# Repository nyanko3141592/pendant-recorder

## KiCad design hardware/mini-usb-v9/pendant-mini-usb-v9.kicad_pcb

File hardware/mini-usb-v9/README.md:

# Mini USB v9 — 回路・丸形収納の比較試作

2026-10-25。USB-Cデータ書き出し＋充電、連続16時間、専用台なし、無線なしを維持する設計案。**発注不可。** 回路図と実フットプリント配置は更新したが、配線完成版ではない。

## 今回の変更

- 実装80点→68点（パッド等を含め74フットプリント）。STM32U535CEU6のQFN48は維持。高価なWLCSP/HDIへの変更を避け、4層の配線成立性を試験中。4層化は未資格化。
- T5838＋TXS0104E＋1.8V LDOを、3.3V直結PDMのIM69D130に変更。AAD/WAKE/THSELを削除。0.768MHz・16kHz/48倍デシメーションを評価候補とする。低電力モードはSNR64dBで、静かな声の音質と電力を実機比較する。データシートの0.3mAは1.8V条件であり、3.3Vでの実測値ではない。
- BQ25185で充電と電源切替を統合。24kΩで4.2V/入力100mA、15kΩで充電20mA候補。SYS10µFの実効容量、ISET10nF、低電圧・ピーク負荷は要検証。
- 温度保護は削除しない。TLV7042の2つのオープンドレイン出力でQ4ゲートをクランプ。MCU許可信号→10kΩ→ゲート、ゲート100kΩプルダウン。冷・熱のどちらか異常ならゲートLow、Q4 OFF、CEのVBUS100kΩプルアップで充電停止。MCUリセット時も許可なし。理想論理のみ確認、POR/瞬断/短絡/公差は未資格化。
- 電池NTCは外部窓比較器で監視。BQ25185内蔵TSの固定10kΩを温度センサー扱いしない。既存10k/B3370仮定の狭い充電窓（公称約20–30℃）を保持。実際のパック仕様が未確定なので設定値も最終値ではない。
- LEDを1個に集約。表示要求時の点滅で残量表示、常時点灯を避ける。
- 記憶容量を4GB→512MiBのCSNP4GCR01-DPWに変更した価格削減候補。LCSC公開表示は欠品。データシートのピン配置は確認済みだがフットプリント製造受理は未確認。4GB版への復帰は同じ収納包絡内で可能性があるものの、ランド再照合が必要。

## 収納

新案26×28×14mm、平面R12.9、縁R2。旧印刷基準26×31×14mm・R5を上書きしていない。正面面積は約25.4%減。OmiのD25.5×15mm寸法包絡比では正面面積約14.6%増。Omi模型は円筒の寸法ゲージで、実製品CADではない。

基板は24×26mmカプセルをUSB側y=24.5mmで切った形。0.8mm厚、下面z=8.5mm。電池15×17×6mm、100mAh候補包絡は維持。低い部品を基板裏に回し、電池上端との公称隙間を確保。電池の保護基板・完成リード・コネクタ配線・膨張公差は未資格化。ケースはテープ仮止め、2点仮支持で、量産用の爪・紐穴・防水・音道シールではない。

## 検査結果

- `erc.json`: ERC 0。
- `drc.json`: 未配線配置原本の幾何DRC 0、回路図等価性0、未配線175件。これを配線済みと扱わない。
- `route-trial.kicad_pcb`: 4層の試験配線。`route-trial-drc.json`に15違反、5未接続。GND面・USB差動/リターンパス・デカップリング配線の再設計が必要。製造用Gerberは出していない。
- 実部品の寸法ではなく、フットプリント外接矩形＋仮高さの保守的な立体包絡。ケース/蓋と部品/電池に重なりなし。部品と電池も重なりなし。支持面の接触あり。
- 5組のSTL/3MFで閉メッシュ、法線整合、単一接続体、正体積、Z=0、mm単位を確認。全三角形間の自己交差を網羅検査したものではない。
- Bambu A1 mini 0.4/PLA/0.2mm/3壁/15%/サポートありで4部品スライス完了。推定23分1秒・5.04g。プリンタ送信/物理印刷は未実施。

## 16時間の条件とトレードオフ

100mAhの70%を使えると仮定すると、平均消費電流は4.375mA以下が必要。達成は未実測。電池の容量を先に減らしていない。

512MiBでは16kHzモノラルIMA-ADPCM、10秒ごとのWAVをage v1暗号化、4KiBクラスタ・暗号化余裕1KiB/区間と仮定し16時間で495,452,160byte。FS予備16MiBを引いた残りは24,641,536byte。実CSD容量/実ファイルサイズ/空き容量検査が必要で、複数日録音や16時間PCM16には使えない。自動削除・上書きはしない。

## 資料

- `pendant-mini-usb-v9.kicad_sch` / `schematic.pdf` / `design.json`: ピン単位回路原本。
- `pendant-mini-usb-v9.kicad_pcb`: 未配線配置原本。`route-trial.*`は別の試験。
- `connections.csv` / `bom.csv`: 設計確認用。JLC発注承認済みBOMではない。
- `review.json`: 電力・容量の算術、理想論理表、発注前と実機の残件。
- モデル: `/Users/takahashinaoki/Downloads/Pendant-mini-usb-v9/`
- 比較原本: `/Users/takahashinaoki/Downloads/Pendant-rounded-fit-v7/`
- 再生成スクリプトは配置/回路を上書きする。手修正後には無条件で再実行しない。

## 出典・調達の状態

2026-10-25閲覧。カタログ掲載は在庫確保・見積り画面の照合完了を意味しない。

- [Infineon IM69D130 datasheet](https://www.infineon.com/dgdl/Infineon-IM69D130-DS-v01_00-EN.pdf): 3.3V直結、PDM、端子、低電力モードの根拠。JLC候補[C536262](https://jlcpcb.com/partdetail/InfineonTechnologies-IM69D130V01/C536262)。末尾発注品番との同一性を要確認。
- [TI BQ25185 datasheet](https://www.ti.com/lit/ds/symlink/bq25185.pdf): 端子・設定・電源経路。JLC候補[C19725033](https://jlcpcb.com/partdetail/TexasInstruments-BQ25185DLHR/C19725033)。[LCSC参考](https://www.lcsc.com/product-detail/C19725033.html?s_z=n_MS2548)は1個$1.7472の表示、PCBA価格ではない。
- [TI TLV7042](https://www.ti.com/product/TLV7042/part-details/TLV7042DDFR): オープンドレイン出力。[LCSC C2867856](https://www.lcsc.com/de/product-detail/C2867856.html)。在庫表示がページ間で相違し未確定。
- [CSNP4GCR01-DPW](https://www.lcsc.com/product-detail/C50396672.html): 512MiB、公開表示欠品・1個参考$12.4734。旧4GBの途中JLC見積り約$40.16/個より低い参考値だが、今回の購入可能価格ではない。総額が安くなることは未確認。
- [Omi consumer hardware](https://docs.omi.me/doc/hardware/consumer): 小型基板、SD NAND、電池と基板の重ね方を参照。専用充電台/無線/HDI加工をそのまま採用していない。

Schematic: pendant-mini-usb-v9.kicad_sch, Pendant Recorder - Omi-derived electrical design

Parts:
C1, C2, C3, C6, C9, C22, C26: 100n; C_0402_1005Metric
C4: 10u; C_0603_1608Metric
C5: 4.7u; C_0603_1608Metric
C7, C16, C25: 1u; C_0402_1005Metric
C11, C12: 10p tentative; C_0402_1005Metric
C13: 2.2u 10V; C_0402_1005Metric
C14: 2.2u; C_0402_1005Metric
C15: 10u 10V effective >=1u; C_0603_1608Metric
C27: 22u effective TBD; C_0603_1608Metric
C28: 10n; C_0402_1005Metric
C29: 100n 10V; C_0402_1005Metric
C30: 10n tentative; C_0402_1005Metric
D6: amber LED 0402 TBD; LED_0402_1005Metric
J1: USB4105-GF-A (candidate); USB_C_GCT_USB4105_GroundLand112
J2: 0781710003 / 100mAh protected NTC pack TBD; Molex_Pico-EZmate_78171-0003_1x03-1MP_P1.20mm_Vertical
J3: TC2030 SWD target pads; Tag-Connect_TC2030-IDC-NL_2x03_P1.27mm_Vertical
Q3: 2N7002 (VBUS detect); SOT-23
Q4: 2N7002; SOT-23
R1: 0R; R_0402_1005Metric
R2: 10k; R_0402_1005Metric
R3, R4, R12, R13, R15, R22, R36: 100k; R_0402_1005Metric
R6, R7: 5.1k 1%; R_0402_1005Metric
R8, R9: 0R tuning; R_0402_1005Metric
R10: 15k 1%; R_0402_1005Metric
R11: 20k 1%; R_0402_1005Metric
R14: 1M; R_0402_1005Metric
R21, R23: 22R tentative; R_0402_1005Metric
R24, R25, R28: 47k; R_0402_1005Metric
R32: 6.8k tentative; R_0402_1005Metric
R33, R34: 1M 1%; R_0402_1005Metric
R35, R37, R38, R40, R43: 10k 1%; R_0402_1005Metric
R39: 12.1k 1%; R_0402_1005Metric
R41: 8.25k 1%; R_0402_1005Metric
R42: 24k 1%; R_0402_1005Metric
SW1: B3U-1000P (candidate); SW_SPST_B3U-1000P
TP1, TP2, TP3, TP5, TP6: TestPoint; TestPoint_Pad_D1.0mm
U1: STM32U535CEU6; QFN-48-1EP_7x7mm_P0.5mm_EP5.6x5.6mm
U2: USBLC6-2P6; SOT-666
U3: BQ25185DLHR; Texas_DLH0010A_WSON-10-1EP_2.2x2mm_P0.4mm_EP0.9x1.5mm
U4: TPS7A0233PDBVR; SOT-23-5
U8: IM69D130V01XTSA1; Infineon_PG-LLGA-5-1
U10: TPS22916CYFPR; TPS22916_YFP4
U11: CSNP4GCR01-DPW; CSNP4GCR01_DPW_LGA8
U12: TLV7042DDFR; SOT-23-8
Y1: 32.768kHz CL=7pF TBD; Crystal_SMD_2012-2Pin_2.0x1.2mm

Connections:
/BAT: C14.1, J2.1 (PACK+), R33.1, TP1.1, U3.2 (BAT)
/BAT_ADC: C28.1, R33.2, R34.1, U1.11 (PA1)
/BAT_TS: J2.2 (PACK_NTC), R37.2, U12.2 (INA-), U12.5 (INB+)
/BOOT0: R3.1, U1.44 (PH3)
/BUTTON_N: R4.2, SW1.1, U1.26 (PB13)
/CC1: J1.A5 (CC1), R6.1
/CC2: J1.B5 (CC2), R7.1
/CHARGER_TS: R35.1, U3.6 (TS_MR)
/CHG_ALLOW: R43.1, U1.20 (PB2)
/CHG_GUARD_GATE: Q4.1 (G), R36.1, R43.2, U12.1 (OUTA), U12.7 (OUTB)
/CHG_INHIBIT_GATE: Q4.3 (D), R12.2, U3.4 (CE_N)
/CHG_N: R11.2, U1.27 (PB14), U3.9 (STAT1)
/GND: C1.2, C2.2, C3.2, C4.2, C5.2, C6.2, C7.2, C9.2, C11.2, C12.2, C13.2, C14.2, C15.2, C16.2, C22.2, C25.2, C26.2, C27.2, C28.2, C29.2, C30.2, D6.1 (K), J1.A1 (GND), J1.A12 (GND), J1.B1 (GND), J1.B12 (GND), J1.SH (SHIELD), J2.3 (PACK-), J3.5 (GND), Q3.2 (S), Q4.2 (S), R3.2, R6.2, R7.2, R10.2, R14.2, R22.2, R34.2, R35.2, R36.2, R39.2, R41.2, R42.2, SW1.2, TP6.1, U1.8 (VSSA), U1.23 (VSS), U1.35 (VSS), U1.47 (VSS), U1.49 (VSS), U2.2 (GND), U3.5 (GND), U3.11 (EP), U4.2 (GND), U8.4 (SELECT), U8.5 (GND), U10.B1 (GND), U11.4 (VSS), U12.4 (VEE)
/ILIM_VSET: R42.1, U3.7 (ILIM_VSET)
/ISET: C30.1, R10.1, U3.8 (ISET)
/LSE_IN: C11.1, U1.3 (PC14), Y1.1
/LSE_OUT: C12.1, U1.4 (PC15), Y1.2
/NRST: C9.1, J3.3 (nRESET), R2.2, U1.7 (NRST)
/PDM_CLK: R21.2, U8.3 (CLOCK)
/PDM_CLK_MCU: R21.1, U1.39 (PB3)
/PDM_DATA: U1.40 (PB4), U8.1 (DATA)
/SD_CLK: R23.2, U11.3 (CLK)
/SD_CLK_MCU: R23.1, U1.15 (PA5)
/SD_CS_N: R28.2, U1.14 (PA4), U11.2 (CS_N)
/SD_EN: R22.1, U1.18 (PB0), U10.B2 (ON)
/SD_MISO: R25.2, U1.16 (PA6), U11.6 (DO)
/SD_MOSI: R24.2, U1.17 (PA7), U11.5 (DI)
/SD_V3: C26.1, C27.1, R24.1, R25.1, R28.1, TP5.1, U10.A1 (VOUT), U11.8 (VCC)
/STATUS_LED: R32.1, U1.29 (PA8)
/STATUS_LED_A: D6.2 (A), R32.2
/SWCLK: J3.4 (SWCLK), U1.37 (PA14)
/SWDIO: J3.2 (SWDIO), U1.34 (PA13)
/SYS: C15.1, TP2.1, U3.1 (SYS), U4.1 (IN), U4.3 (EN)
/TS_COLD_REF: R38.2, R39.1, U12.3 (INA+)
/TS_HOT_REF: R40.2, R41.1, U12.6 (INB-)
/USB_DM: J1.A7 (D-), J1.B7 (D-), R9.1, U2.3 (IO2), U2.4 (IO2)
/USB_DM_MCU: R9.2, U1.32 (PA11)
/USB_DP: J1.A6 (D+), J1.B6 (D+), R8.1, U2.1 (IO1), U2.6 (IO1)
/USB_DP_MCU: R8.2, U1.33 (PA12)
/V3V3: C1.1, C2.1, C3.1, C4.1, C16.1, C22.1, C25.1, J3.1 (VTref), R1.1, R2.1, R4.1, R11.1, R15.1, TP3.1, U1.1 (VBAT), U1.24 (VDD), U1.36 (VDD), U1.48 (VDD), U4.5 (OUT), U8.2 (VDD), U10.A2 (VIN)
/VBUS: C13.1, C29.1, J1.A4 (VBUS), J1.A9 (VBUS), J1.B4 (VBUS), J1.B9 (VBUS), R12.1, R13.1, R37.1, R38.1, R40.1, U2.5 (VBUS), U3.10 (IN), U12.8 (VCC)
/VBUS_GATE: Q3.1 (G), R13.2, R14.1
/VBUS_N: Q3.3 (D), R15.2, U1.10 (PA0)
/VCAP: C5.1, U1.22 (VCAP)
/VDDA: C6.1, C7.1, R1.2, U1.9 (VDDA)

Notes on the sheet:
01 MCU / RTC / UI
02 USB-C / CHARGER
03 POWER / FUEL GAUGE
04 AUDIO / SD / INDICATORS
ENGINEERING DRAFT - NOT FOR FABRICATION - See hardware/mini-usb-v9/README.md

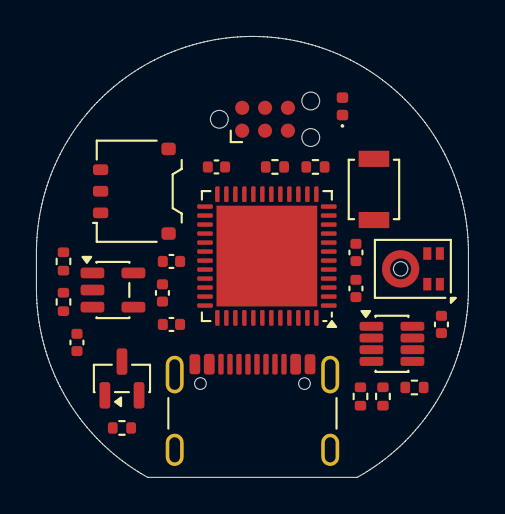
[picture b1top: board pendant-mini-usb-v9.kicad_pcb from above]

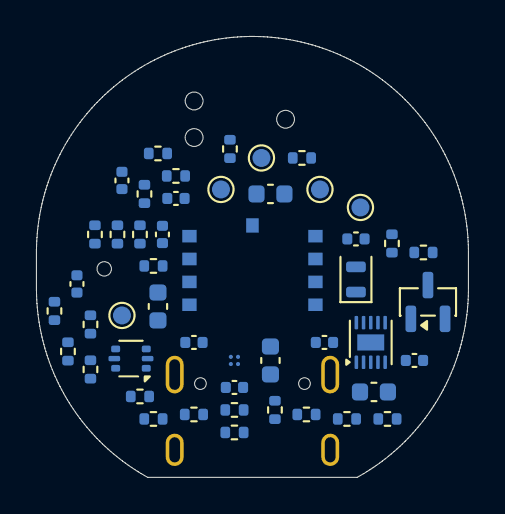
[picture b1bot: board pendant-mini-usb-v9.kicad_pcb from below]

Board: 4 copper layers, 24.0 x 24.5 mm, 74 parts (48 on the bottom side), 45 nets, no tracks yet.

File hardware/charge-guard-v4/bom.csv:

Reference,Part/value,Footprint,Design note
U1,STM32U535CEU6,Package_DFN_QFN:QFN-48-1EP_7x7mm_P0.5mm_EP5.6x5.6mm,512KB Flash/274KB RAM; non-SMPS UFQFPN48. PB3/PB4 ADF AF3; PA5/6/7 SPI1 AF5. VDD USB shared 3.3V. JLC acceptance and pin review pending.
C1,100n,Capacitor_SMD:C_0402_1005Metric,
C4,10u,Capacitor_SMD:C_0603_1608Metric,Main bulk capacitor; check startup and effective capacitance.
C9,100n,Capacitor_SMD:C_0402_1005Metric,
R2,10k,Resistor_SMD:R_0402_1005Metric,
Y1,32.768kHz CL=7pF TBD,Crystal:Crystal_SMD_2012-2Pin_2.0x1.2mm,
C11,10p tentative,Capacitor_SMD:C_0402_1005Metric,
C12,10p tentative,Capacitor_SMD:C_0402_1005Metric,
J3,TC2030 SWD target pads,Connector:Tag-Connect_TC2030-IDC-NL_2x03_P1.27mm_Vertical,TC2030-NL/CTX standard; completed STM32-compatible probe/cable; access with battery disconnected.
SW1,B3U-1000P (candidate),Button_Switch_SMD:SW_SPST_B3U-1000P,
R4,100k,Resistor_SMD:R_0402_1005Metric,
R5,3.3k,Resistor_SMD:R_0402_1005Metric,
D1,red LED,LED_SMD:LED_0402_1005Metric,
J1,USB4105-GF-A (candidate),PendantD1:USB_C_GCT_USB4105_GroundLand112,Exact footprint and shield pad numbering pending connector selection
R6,5.1k 1%,Resistor_SMD:R_0402_1005Metric,
R7,5.1k 1%,Resistor_SMD:R_0402_1005Metric,
R8,0R tuning,Resistor_SMD:R_0402_1005Metric,STM32 integrated USB termination; external series value validate against ST USB layout guidance.
R9,0R tuning,Resistor_SMD:R_0402_1005Metric,STM32 integrated USB termination; external series value validate against ST USB layout guidance.
U2,USBLC6-2P6,Package_TO_SOT_SMD:SOT-666,"ST DS4260 same 6-pin function diagram; smaller package, LCSC C15999 catalog; orientation/land pattern final audit pending."
C13,2.2u 10V,Capacitor_SMD:C_0402_1005Metric,
U3,BQ25101YFPR,Pendant:BQ25101_YFP6,BQ25101 charge regulation retained; TS driven by independent hardware window guard and fixed10k. Not directly connected to pack NTC.
R10,6.19k 1%,Resistor_SMD:R_0402_1005Metric,"Nominal21.81mA, upper estimate23.66mA. XE charge current/termination/voltage acceptance not finalized."
R11,100k,Resistor_SMD:R_0402_1005Metric,
C14,2.2u,Capacitor_SMD:C_0402_1005Metric,
J2,0781710003 / DTP401525-XE,Connector_Molex:Molex_Pico-EZmate_78171-0003_1x03-1MP_P1.20mm_Vertical,"Pack NTC goes to separate window comparator, not charger TS. Beta/tolerances need supplier confirmation."
Q2,2N7002 (charge inhibit),Package_TO_SOT_SMD:SOT-23,Default-on TS clamp. Only MCU permission AND both hardware temperature permissions release it. Validate start-up transients.
R12,100k,Resistor_SMD:R_0402_1005Metric,100k VBUS pull-up defaults Q2 to charge inhibited; no MCU GPIO connection to5V.
D2,BAT54WS (candidate; leakage/forward drop review pending),Diode_SMD:D_SOD-323,USB path; characterize leakage and input inrush
Q1,DMP2035U (candidate; power path review pending),Package_TO_SOT_SMD:SOT-23,"S=SYS, D=BAT intentionally; body diode BAT -> SYS; exact MPN/pinout pending"
R16,100k,Resistor_SMD:R_0402_1005Metric,
C15,4.7u,Capacitor_SMD:C_0603_1608Metric,
U4,TPS7A0233PDBVR,Package_TO_SOT_SMD:SOT-23-5,3.3V main rail: 48-pin MCU has no separate USB supply; dropout/capacity measurement required.
U6,TPS7A0218PDBVR,Package_TO_SOT_SMD:SOT-23-5,DBV / SOT23-5 prototype; miniaturization later
C16,1u,Capacitor_SMD:C_0402_1005Metric,
C18,1u,Capacitor_SMD:C_0402_1005Metric,
C19,1u,Capacitor_SMD:C_0402_1005Metric,
R17,100k,Resistor_SMD:R_0402_1005Metric,
U8,T5838,Pendant:T5838_LGA7_BottomPort,BOTTOM port; 1.62..1.98V only; SELECT low = right channel
U9,TXS0104ERUTR,Package_DFN_QFN:Texas_R-PUQFN-N12,TI SCES651K Table 5-4 RUT pinout. UQFN procurement and PCBA acceptance pending.
R21,22R tentative,Resistor_SMD:R_0402_1005Metric,
C22,100n,Capacitor_SMD:C_0402_1005Metric,
C23,100n,Capacitor_SMD:C_0402_1005Metric,
C24,100n,Capacitor_SMD:C_0402_1005Metric,
U10,TPS22916CYFPR,Pendant:TPS22916_YFP4,Omi SD switch; power-off sequence must tristate ALL SD signals
R22,100k,Resistor_SMD:R_0402_1005Metric,
C25,1u,Capacitor_SMD:C_0402_1005Metric,
U11,CSNP32GCR01-BOW,Pendant:CSNP32GCR01_LGA8,SPI mode per manufacturer p2; unused DAT1/DAT2 reserved; verify power-up and interrupted-write behavior.
R23,22R tentative,Resistor_SMD:R_0402_1005Metric,
R24,47k,Resistor_SMD:R_0402_1005Metric,
R25,47k,Resistor_SMD:R_0402_1005Metric,
R28,47k,Resistor_SMD:R_0402_1005Metric,
C26,100n,Capacitor_SMD:C_0402_1005Metric,
C27,22u effective TBD,Capacitor_SMD:C_0603_1608Metric,
TP1,TestPoint,TestPoint:TestPoint_Pad_D1.0mm,
TP2,TestPoint,TestPoint:TestPoint_Pad_D1.0mm,
TP3,TestPoint,TestPoint:TestPoint_Pad_D1.0mm,
TP4,TestPoint,TestPoint:TestPoint_Pad_D1.0mm,
TP5,TestPoint,TestPoint:TestPoint_Pad_D1.0mm,
TP6,TestPoint,TestPoint:TestPoint_Pad_D1.0mm,
R32,6.8k tentative,Resistor_SMD:R_0402_1005Metric,"LED current target 0.1-0.2mA; verify LED Vf, daylight readability and GPIO limits"
D6,amber LED 0402 TBD,LED_SMD:LED_0402_1005Metric,Battery level by blink count; shared charging/error indication; exact LED MPN pending.
C2,100n,Capacitor_SMD:C_0402_1005Metric,
C3,100n,Capacitor_SMD:C_0402_1005Metric,
C5,4.7u,Capacitor_SMD:C_0603_1608Metric,
C6,100n,Capacitor_SMD:C_0402_1005Metric,
C7,1u,Capacitor_SMD:C_0402_1005Metric,
R1,0R,Resistor_SMD:R_0402_1005Metric,
R3,100k,Resistor_SMD:R_0402_1005Metric,
Q3,2N7002 (VBUS detect),Package_TO_SOT_SMD:SOT-23,
R13,100k,Resistor_SMD:R_0402_1005Metric,
R14,1M,Resistor_SMD:R_0402_1005Metric,
R15,100k,Resistor_SMD:R_0402_1005Metric,
R33,1M 1%,Resistor_SMD:R_0402_1005Metric,"Battery divider 1:2; sample after settling, calibrate with VREFINT; not coulomb counting."
R34,1M 1%,Resistor_SMD:R_0402_1005Metric,"Battery divider 1:2; sample after settling, calibrate with VREFINT; not coulomb counting."
C28,10n,Capacitor_SMD:C_0402_1005Metric,"Battery divider 1:2; sample after settling, calibrate with VREFINT; not coulomb counting."
R35,10k 1%,Resistor_SMD:R_0402_1005Metric,Holds normal TS level when released; no floating TS/TTDM in intended circuit.
R36,100k,Resistor_SMD:R_0402_1005Metric,MCU reset/high-Z defaults to no charging permission.
R37,10k 1%,Resistor_SMD:R_0402_1005Metric,Ratiometric NTC excitation only while USB present; self-heating must be verified.
R38,10k 1%,Resistor_SMD:R_0402_1005Metric,
R39,12.1k 1%,Resistor_SMD:R_0402_1005Metric,Provisional narrow window. Final values require actual pack R-T curve.
R40,10k 1%,Resistor_SMD:R_0402_1005Metric,
R41,8.25k 1%,Resistor_SMD:R_0402_1005Metric,Provisional narrow window. Final values require actual pack R-T curve.
U12,TLV7032DDFR,Package_TO_SOT_SMD:SOT-23-8,Push-pull variant intentionally selected: POR outputs low. Do not substitute TLV7042 open-drain (POR high-Z). TI SLVSE13J pinout table4-2.
Q4,2N7002,Package_TO_SOT_SMD:SOT-23,Series pull-down permission chain. All three must conduct to release Q2. Body diodes oppose pull-down when off. Verify stack/leakage/transients.
Q5,2N7002,Package_TO_SOT_SMD:SOT-23,Series pull-down permission chain. All three must conduct to release Q2. Body diodes oppose pull-down when off. Verify stack/leakage/transients.
Q6,2N7002,Package_TO_SOT_SMD:SOT-23,Series pull-down permission chain. All three must conduct to release Q2. Body diodes oppose pull-down when off. Verify stack/leakage/transients.
C29,100n 10V,Capacitor_SMD:C_0402_1005Metric,Place adjacent to U12 supply pins.

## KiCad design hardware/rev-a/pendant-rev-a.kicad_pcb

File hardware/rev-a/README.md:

# Pendant Recorder Rev A1 — 回路・配置レビュー用

> 製造方針: [JLCPCBで部品実装まで依頼](../../docs/jlcpcb-assembly.md)。両面Standard PCBAを第一候補とし、実装用在庫・全フットプリント・製造レビューを確認して採用する。現回路の全品番受理は未確認。

2026-10-24。**未配線の配置検討版。発注不可。** 回路図から92部品を実寸フットプリントに割り当て、ネット接続付きの4層KiCad基板を作成した。20×34×0.8mmは現在の配置検討枠で、最小寸法や配線成立を示すものではない。

- [基板配置と製造上の課題](layout-review.md)
- [基板データ](pendant-rev-a.kicad_pcb)、[表面](placement-top.svg)、[裏面](placement-bottom.svg)
- [回路図プレビュー](pendant-rev-a.svg) / [検査記録](verification.md)
- `design.json`: 部品、端子、ネット、フットプリントの原本
- `Pendant.pretty/`: データシートから作成したフットプリント。製造監査は未完了
- `bom.csv` / `connections.csv`: 候補部品表と全端子接続表
- `placement-review.csv`: 配置確認用。JLC発注用CPLではない

既製DTP401525(PHR)110mAh（最大15.5×27×4.2mm、付属PHコネクタと配線は別枠）を第一候補とする。24時間録音・平均2mA以下は未実測の設計目標。旧円形26mmモデルや20×32×12mm案は、現配置が入ることを保証しない。

## 既存案からの必須修正

1. **STM32U535CBU6ではSDMMCを接続できない。** ST公式のUFQFPN48端子データにSDMMC信号がない。試作は **STM32U535RCT6 / LQFP64、内部LDO版**。PC8/9/10/11/12、PD2を使用する。22mm円形の量産候補はUFBGA64等を別途選定し、端子表と配置をやり直す。LQFP64案が22mmに収まるとは主張しない。
2. **T5838は1.8V専用、底面音孔。** 最新DS-000383 v1.2では1.62〜1.98V、絶対最大も1.98V。既存の3V直結案は不可。OmiのMIC1回路を参考に1.8V LDO＋TXS0104Eを入れた。基板の音孔とガスケットが必要。
3. USB PHYには **VBUSから専用3.3V LDO→VDDUSB**。録音用3.0Vとは分け、USBの電源条件を満たす設計とする。USB切断時のVDDUSB=0、電源監視・USB起動順序はST資料と実機で検証する。
4. BQ25101のBATにMSC負荷を直接ぶら下げない。USB中はD2からSYSへ給電し、Q1で電池からSYSへの経路を遮断する。これにより充電電流に同期中のシステム負荷が混ざるのを避ける。
5. 110mAh電池の充電設定は**約21.8mA**。RISET=6.19kΩ（1%）、135/6190=0.02181A。KISET最大145と抵抗公差から最大約23.66mA。パックの標準22mAに近づけ、最大55mAを下回る設定へ変更。充電時間はCC部分だけでも約5時間相当で、CVを含む時間は実測で確定する。

## Omiからの継承と差分

基準: `reference/omi/hardware-consumer/mainboard-schematic.pdf` の実際のタイトルは **OMI 2 v0.5、5ページ**。上流のフォルダ/READMEのv1.2表記と区別する。

| Omi回路 | 本設計 |
|---|---|
| Sheet 4 MIC1 T5838、1.8V、TXS0104E、100nF、SELECT=GND | 電圧と信号構成を継承。LDOを低Iq品へ変更。1マイクで開始 |
| Sheet 4 SD NAND + TPS22916、スイッチ後電源へのプルアップ | 継承。512MB→4GB、SPI→SDMMC 4bit。CMD/DAT0〜3の5本をプルアップ |
| Sheet 5 BQ25101、ISET、10k NTC、入出力2.2µF | 継承。約21.8mA設定、保護付きセル、外付け負荷分離、充電停止GPIO追加 |
| Sheet 2 SWD、32kHz水晶 | 構成を参考にし、STM32固有の端子とVCAPに変更 |
| 無線SoC、Wi-Fi、RF、IMU、振動モーター、磁気充電台 | 非搭載。USB-Cを本体へ直付け |
| 生セクタのリングバッファ | 不採用。FAT上の通常WAVファイル |

参照ファイルは改変せず、MITライセンスを保持している。

## 接続の要点

| 機能 | STM32ポート / LQFP64端子 | 接続 |
|---|---|---|
| SD DAT0/1/2/3 | PC8/9/10/11 = 39/40/51/52 | NAND 6/7/1/2 |
| SD CLK / CMD | PC12 / PD2 = 53/54 | 22Ω経由NAND 3 / NAND 5 |
| ADF CLK / DATA | PB3 / PB4 = 55/56 | TXS B4 / B3。PC10/11のADF機能はSDと競合するため使わない |
| MIC WAKE / THSEL | PA2 / PA3 = 16/17 | TXS B1 / B2 |
| USB D− / D+ | PA11 / PA12 = 44/45 | 22Ω仮値、ESD、USB-C両面端子 |
| I2C SCL / SDA | PB6 / PB7 = 58/59 | MAX17048、4.7kΩ→V3 |
| SWDIO / SWCLK | PA13 / PA14 = 46/49 | パッド。VTrefは電圧参照のみ |
| SD_EN / MIC_EN | PB0 / PB1 = 26/27 | 起動時プルダウンでOFF |
| USB検出 | PA0 = 14 | Q3経由、**VBUS_N=Lowで接続** |
| 電池割り込み / 充電状態 | PA1 / PB14 = 15/35 | Active low |
| 充電禁止 | PB2 = 28 | High→Q2→TSをGNDへ。通常はLow |
| 録音LED / ボタン | PB12 / PB13 = 33/34 | D1 High点灯、ボタンLow |
| 残量3点LED | PA4/5/6 = 20/21/22 | R29/30/31→D3/4/5、High点灯 |
| 状態LED | PA7 = 23 | R32→D6、High点灯。充電/同期/異常 |
| LSE | PC14/15 = 3/4 | 32.768kHz、容量は水晶確定後に計算 |

VDD 19/32/64はそれぞれ100nF、共通10µF。VCAP 30は4.7µFで他負荷禁止。VDDAは0Ω経由V3＋100nF/1µF。VBAT端子はV3で、電池直結ではない。保護遮断時はRTCを失う。

### 電源経路

- 持ち歩き: 保護済みBAT→Q1→SYS→3.0V LDO→MCU/SD。マイクのみ1.8V。
- USB接続: VBUS→D2→SYS。同時にVBUS→BQ25101→BAT、VBUS→3.3V LDO→VDDUSB。
- **Q1はsource=SYS、drain=BAT**。ボディダイオードをBAT→SYS向きにする。通常の高側スイッチと見た目が逆なのでフットプリント照合必須。gate=VBUS、100kΩでGNDへ。低VGSでのRDS(on)、逆漏れ、最大VGSを満たす型番は未選定。
- MAX17048は保護済みBATに接続。I2CプルアップはV3。保護セルが外れた際のI2C端子からの逆給電も確認対象。
- TSはセルに密着させた10k NTC。電池内蔵NTCとTH1を二重実装しない。NTCを省略したまま使用しない。
- セル保護は電池パックに要求する。BQ25101は過放電/短絡保護回路の代用にはならない。

### USBとSDの所有権

1. VBUS検出だけでは充電のみ。録音ON/OFFを維持し、SDはファームが所有する。同期要求（暫定: USB接続中にボタン2回押し）を受けて初めて録音DMA停止→WAVヘッダ確定→flush/sync→FAT unmount。
2. USB用電源を検証してPHY/MSC開始。MSC中はホストからのブロック要求だけがSDを使用し、ファームのファイル処理は動かさない。
3. USB切断後はMSC処理を停止してからFATをmount。`TIME.TXT`を検査してRTC設定、同期前の録音ON/OFFへ戻す。Macは安全な取り外しを行う。充電のみでの切断はSDを再mountしない。
   - データ接続のない充電器で同期操作をした場合、未接続タイムアウト後にMSCを停止し、ファームがSDを安全に再取得して元の録音状態へ戻す。
4. USB suspendでは充電禁止、SD停止、USB規定内への低消費電力化が必要。起動・未列挙時は総入力100mA以内を設計予算とし、50mA充電＋システムの最悪値を実測する。
5. SD電源OFFはsync/unmount後。CMD/DAT/CLKをHi-ZにしてプルアップはSD_V3のみ。再起動時は低速初期化とACMD6による4bit設定を行う。
6. 電圧低下で新規録音を開始しない。BORで突然切れる前にファイルを閉じる閾値と残時間を実測する。録音ファイルの自動削除は実装しない。

## 発注前に解決する項目

- J1、Q1、D2、水晶、セルの実型番、全フットプリント、ランド/マスク/ステンシル。
- VBUS突入電流。直結容量だけでなくD2下流と充電経路も含め、必要なら電流制限/ソフトスタートを追加。USB suspend、逆流、抜き差しでの電圧低下も実測。
- 3.0V LDOのピーク電流/ドロップアウトとSD_V3≥2.7V。SDの長い内部busyを含めた電力測定。容量/typ値からの平均電流予測は保証ではない。
- TXS0104Eの波形と負荷容量。PDMクロック768kHz、16kHz化のADF設定、SELECT=Lowの受信エッジ、AAD双方向THSELを検証。
- LSEのCL、寄生容量、ESR、起動マージン。仮の10pFをそのまま発注しない。
- メーカーの全電源条件、GPIO AF番号、USBクロックとCRS、CubeMX設定を確認。
- 30mm角4層試作で電流を測る。装着用v1は22mm円形枠への配置とOmi相当の外形（直径約25.5mm・厚さ約15mm）を検証する。12g・16時間録音も未達成の目標。

## 一次資料

- ST package-specific pin data: https://github.com/STMicroelectronics/STM32_open_pin_data/blob/7d1f1514ed5583ec5007ad91236b4e1d377295b1/mcu/STM32U535RCTx.xml （比較: `STM32U535CBUx.xml`）
- ST DS14217: https://www.st.com/resource/en/datasheet/stm32u535cb.pdf
- ST AN5373: https://www.st.com/resource/en/application_note/an5373-getting-started-with-stm32u5-mcu-hardware-development-stmicroelectronics.pdf
- TDK DS-000383 v1.2: https://d17t6iyxenbwp1.cloudfront.net/s3fs-public/2026-01/DS-000383-T5838-Datasheet-v1.2.pdf
- SD NANDメーカー資料（代理店配布）: https://datasheet.lcsc.com/datasheet/pdf/bfa5f23b6901abecebf24c347afa6e3d.pdf?productCode=C5440134
- TI BQ25101: https://www.ti.com/lit/ds/symlink/bq25101.pdf
- TI TPS7A02: https://www.ti.com/lit/ds/symlink/tps7a02.pdf
- TI TXS0104E: https://www.ti.com/lit/ds/symlink/txs0104e.pdf
- TI TPS22916: https://www.ti.com/lit/ds/symlink/tps22916.pdf
- ADI MAX17048: https://www.analog.com/media/en/technical-documentation/data-sheets/MAX17048-MAX17049.pdf
- Omi固定commitと各ファイル: ../../docs/omi-reference.md

充電のみの追加はファームの状態遷移で対応する設計。現在の回路では給電経路とUSBデータ線が分かれているため、現時点で回路図の変更は不要。ファーム実装と電源状態別の試験は未完了。

## インジケーター追加

残量3点（D3〜D5）＋独立した状態LED（D6）を追加。既存D1は録音専用。各追加LEDはGPIO→6.8kΩ（仮）→LED→GND、アンバー0402候補。低電流での輝度とVfを満たす型番は未選定。GPIOはLQFP64の未使用PA4〜PA7を割り当てた。画面やLEDドライバは追加しない。

暫定の駆動電流は追加1点あたり0.1〜0.2mA。実値はVfとGPIO出力電圧に依存する。録音D1が仮に0.3mAで16時間点灯すると4.8mAhを使うため、省電力見積りのLED枠を従来のまま流用しない。電池残量の表示は短時間、録音表示は独立して継続。追加LEDは起動時にGPIOをLowへ初期化し、ファーム状態に応じて表示する。

表示の閾値・優先順位はdocs/requirements.md。本回路のCHGは充電中を示す信号で、Highだけでは完了/無充電/異常を識別できない。MAX17048のSOC≥95%は「満充電付近」の推定表示に限定し、充電終止の確定表示にはしない。温度停止などの詳細識別には追加監視の要否を評価する。

## 発注準備の追記

J3を独自5点から標準TC2030-NLへ変更。[完成書込みケーブルの案](../../docs/solderless-programming.md)を参照。SWOはNC。端子照合282接続＋26 NC、ERC 0。未配線221項目/DRC19件は残る。調達記録はsourcing-review.json、注文用BOMではない。U1/U9のJLCカタログ一致を確認したが確保・全品目実装受理は未完了。既存A2機械モデルはこのJ3変更前の比較案。

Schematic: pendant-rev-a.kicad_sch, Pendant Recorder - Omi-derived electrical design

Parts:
C1, C2, C3, C6, C8, C9, C10, C21, C22, C23, C24, C26: 100n; C_0402_1005Metric
C4: 10u; C_0603_1608Metric
C5, C15: 4.7u; C_0603_1608Metric
C7, C16, C17, C18, C19, C25: 1u; C_0402_1005Metric
C11, C12: 10p tentative; C_0402_1005Metric
C13: 2.2u 10V; C_0402_1005Metric
C14: 2.2u; C_0402_1005Metric
C20: 1u 10V; C_0402_1005Metric
C27: 22u effective TBD; C_0603_1608Metric
D1: red LED; LED_0402_1005Metric
D2: BAT54WS (candidate; leakage/forward drop review p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; D_SOD-323
D3, D4, D5, D6: amber LED 0402 TBD; LED_0402_1005Metric
J1: USB4105-GF-A (candidate); USB_C_Receptacle_GCT_USB4105-xx-A_16P_TopMnt_Horizontal
J2: S2B-PH-SM4-TB(LF)(SN) / DTP401525 110mAh; JST_PH_S2B-PH-SM4-TB_1x02-1MP_P2.00mm_Horizontal
J3: TC2030-CTX-NL-STDC14 target pads; Tag-Connect_TC2030-IDC-NL_2x03_P1.27mm_Vertical
Q1: DMP2035U (candidate; power path review pending); SOT-23
Q2: 2N7002 (charge inhibit); SOT-23
Q3: 2N7002 (VBUS detect); SOT-23
R1: 0R; R_0402_1005Metric
R2: 10k; R_0402_1005Metric
R3, R4, R11, R12, R13, R15, R16, R17, R20, R22: 100k; R_0402_1005Metric
R5: 3.3k; R_0402_1005Metric
R6, R7: 5.1k 1%; R_0402_1005Metric
R8, R9, R21, R23: 22R tentative; R_0402_1005Metric
R10: 6.19k 1%; R_0402_1005Metric
R14: 1M; R_0402_1005Metric
R18, R19: 4.7k; R_0402_1005Metric
R24, R25, R26, R27, R28: 47k; R_0402_1005Metric
R29, R30, R31, R32: 6.8k tentative; R_0402_1005Metric
SW1: B3U-1000P (candidate); SW_SPST_B3U-1000P
TH1: NCP15XH103F03RC 10k NTC; R_0402_1005Metric
TP1, TP2, TP3, TP4, TP5, TP6, TP7: TestPoint; TestPoint_Pad_D1.0mm
U1: STM32U535RCT6; LQFP-64_10x10mm_P0.5mm
U2: USBLC6-2SC6; SOT-23-6
U3: BQ25101YFPR; BQ25101_YFP6
U4: TPS7A0230PDBVR; SOT-23-5
U5: TPS7A0233PDBVR; SOT-23-5
U6: TPS7A0218PDBVR; SOT-23-5
U7: MAX17048G+T10; TDFN-8-1EP_2x2mm_P0.5mm_EP0.8x1.2mm
U8: T5838; T5838_LGA7_BottomPort
U9: TXS0104EYZTR; TXS0104E_YZT12
U10: TPS22916CYFPR; TPS22916_YFP4
U11: CSNP32GCR01-BOW; CSNP32GCR01_LGA8
Y1: 32.768kHz CL=7pF TBD; Crystal_SMD_2012-2Pin_2.0x1.2mm

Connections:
BAT: C14.1, C21.1, J2.1 (PACK+), Q1.3 (D), TP1.1, U3.A1 (OUT), U7.2 (CELL), U7.3 (VDD)
BAT_ALERT_N: R20.2, U1.15 (PA1), U7.5 (ALRT)
BAT_LED_1: R29.1, U1.20 (PA4)
BAT_LED_1_A: D3.2 (A), R29.2
BAT_LED_2: R30.1, U1.21 (PA5)
BAT_LED_2_A: D4.2 (A), R30.2
BAT_LED_3: R31.1, U1.22 (PA6)
BAT_LED_3_A: D5.2 (A), R31.2
BAT_TS: Q2.3 (D), TH1.1, U3.B1 (TS)
BOOT0: R3.1, U1.60 (PH3-BOOT0)
BUTTON_N: R4.2, SW1.1, U1.34 (PB13)
CC1: J1.A5 (CC1), R6.1
CC2: J1.B5 (CC2), R7.1
CHG_DISABLE: Q2.1 (G), R12.1, U1.28 (PB2)
CHG_N: R11.2, U1.35 (PB14), U3.C1 (CHG)
GND: C1.2, C2.2, C3.2, C4.2, C5.2, C6.2, C7.2, C8.2, C9.2, C10.2, C11.2, C12.2, C13.2, C14.2, C15.2, C16.2, C17.2, C18.2, C19.2, C20.2, C21.2, C22.2, C23.2, C24.2, C25.2, C26.2, C27.2, D1.1 (K), D3.1 (K), D4.1 (K), D5.1 (K), D6.1 (K), J1.A1 (GND), J1.A12 (GND), J1.B1 (GND), J1.B12 (GND), J1.SH (SHIELD), J2.2 (PACK-), J3.5 (GND), Q2.2 (S), Q3.2 (S), R3.2, R6.2, R7.2, R10.2, R12.2, R14.2, R16.2, R17.2, R22.2, SW1.2, TH1.2, TP6.1, U1.12 (VSSA), U1.18 (VSS), U1.31 (VSS), U1.47 (VSS), U1.63 (VSS), U2.2 (GND), U3.C2 (VSS), U4.2 (GND), U5.2 (GND), U6.2 (GND), U7.1 (CTG), U7.4 (GND), U7.6 (QSTRT), U7.9 (EP), U8.2 (SELECT), U8.3 (GND), U9.D2 (GND), U10.B1 (GND), U11.4 (VSS)
I2C_SCL: R18.2, U1.58 (PB6), U7.7 (SCL)
I2C_SDA: R19.2, U1.59 (PB7), U7.8 (SDA)
ISET: R10.1, U3.B2 (ISET)
LED_A: D1.2 (A), R5.2
LSE_IN: C11.1, U1.3 (PC14-OSC32_IN), Y1.1
LSE_OUT: C12.1, U1.4 (PC15-OSC32_OUT), Y1.2
MIC_CLK_1V8: U8.6 (CLK), U9.D3 (A4)
MIC_DATA_1V8: U8.1 (DATA), U9.C3 (A3)
MIC_EN: R17.1, U1.27 (PB1), U6.3 (EN)
MIC_THSEL: U1.17 (PA3), U9.B1 (B2)
MIC_THSEL_1V8: U8.5 (THSEL), U9.B3 (A2)
MIC_WAKE: U1.16 (PA2), U9.A1 (B1)
MIC_WAKE_1V8: U8.4 (WAKE), U9.A3 (A1)
NRST: C9.1, J3.3 (nRESET), R2.2, U1.7 (NRST)
PDM_CLK: R21.2, U9.D1 (B4)
PDM_CLK_MCU: R21.1, U1.55 (PB3)
PDM_DATA: U1.56 (PB4), U9.C1 (B3)
REC_LED: R5.1, U1.33 (PB12)
SD_CLK: R23.2, U11.3 (CLK)
SD_CLK_MCU: R23.1, U1.53 (PC12)
SD_CMD: R24.2, U1.54 (PD2), U11.5 (CMD)
SD_D0: R25.2, U1.39 (PC8), U11.6 (DAT0)
SD_D1: R26.2, U1.40 (PC9), U11.7 (DAT1)
SD_D2: R27.2, U1.51 (PC10), U11.1 (DAT2)
SD_D3: R28.2, U1.52 (PC11), U11.2 (DAT3)
SD_EN: R22.1, U1.26 (PB0), U10.B2 (ON)
SD_V3: C26.1, C27.1, R24.1, R25.1, R26.1, R27.1, R28.1, TP5.1, U10.A1 (VOUT), U11.8 (VCC)
STATUS_LED: R32.1, U1.23 (PA7)
STATUS_LED_A: D6.2 (A), R32.2
SWCLK: J3.4 (SWCLK), U1.49 (PA14)
SWDIO: J3.2 (SWDIO), U1.46 (PA13)
SYS: C15.1, D2.1 (K), Q1.2 (S), TP2.1, U4.1 (IN), U4.3 (EN)
USB_DM: J1.A7 (D-), J1.B7 (D-), R9.1, U2.3 (IO2), U2.4 (IO2)
USB_DM_MCU: R9.2, U1.44 (PA11)
USB_DP: J1.A6 (D+), J1.B6 (D+), R8.1, U2.1 (IO1), U2.6 (IO1)
USB_DP_MCU: R8.2, U1.45 (PA12)
V1V8: C18.1, C22.1, C23.1, TP4.1, U6.5 (OUT), U8.7 (VDD), U9.B2 (VCCA), U9.C2 (OE)
V3: C1.1, C2.1, C3.1, C4.1, C10.1, C16.1, C19.1, C24.1, C25.1, J3.1 (VTref), R1.1, R2.1, R4.1, R11.1, R15.1, R18.1, R19.1, R20.1, TP3.1, U1.1 (VBAT), U1.19 (VDD), U1.32 (VDD), U1.64 (VDD), U4.5 (OUT), U6.1 (IN), U9.A2 (VCCB), U10.A2 (VIN)
VBUS: C13.1, C20.1, D2.2 (A), J1.A4 (VBUS), J1.A9 (VBUS), J1.B4 (VBUS), J1.B9 (VBUS), Q1.1 (G), R13.1, R16.1, U2.5 (VBUS), U3.A2 (IN), U5.1 (IN), U5.3 (EN)
VBUS_GATE: Q3.1 (G), R13.2, R14.1
VBUS_N: Q3.3 (D), R15.2, TP7.1, U1.14 (PA0)
VCAP: C5.1, U1.30 (VCAP)
VDDA: C6.1, C7.1, R1.2, U1.13 (VDDA)
VUSB3V3: C8.1, C17.1, U1.48 (VDDUSB), U5.5 (OUT)

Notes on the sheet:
01 MCU / RTC / UI
02 USB-C / CHARGER
03 POWER / FUEL GAUGE
04 AUDIO / SD / INDICATORS
A1 ENGINEERING DRAFT - NOT FOR FABRICATION - See hardware/rev-a/README.md

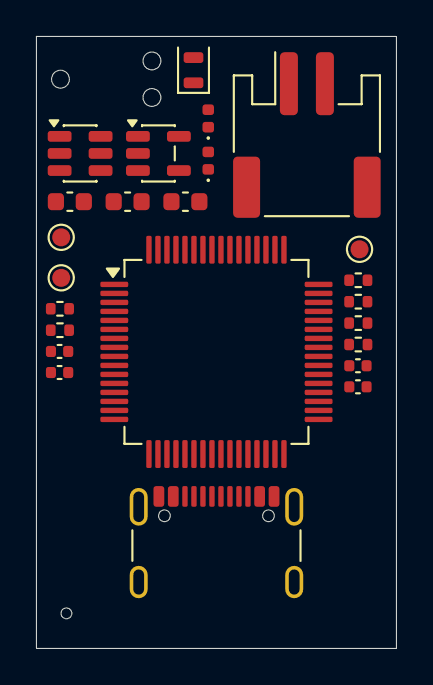
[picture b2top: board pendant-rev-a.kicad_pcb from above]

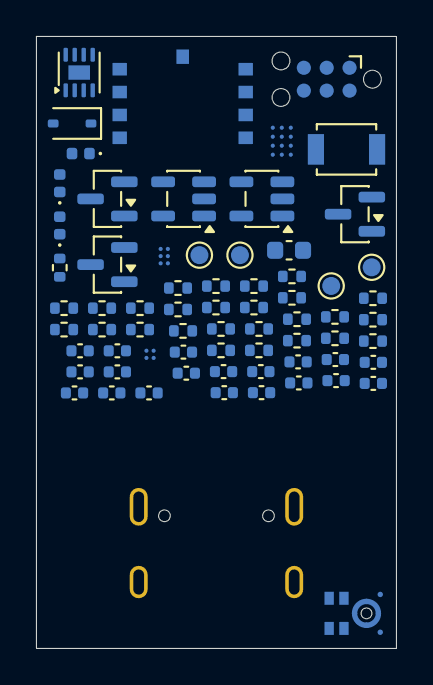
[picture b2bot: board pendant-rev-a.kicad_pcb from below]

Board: 4 copper layers, 20.0 x 34.0 mm, 92 parts (68 on the bottom side), 60 nets, no tracks yet.

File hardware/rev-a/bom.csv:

Reference,Part/value,Footprint,Design note
U1,STM32U535RCT6,Package_QFP:LQFP-64_10x10mm_P0.5mm,"LQFP64, LDO-only; 48-pin CBU6 rejected: no SDMMC pins"
C1,100n,Capacitor_SMD:C_0402_1005Metric,
C2,100n,Capacitor_SMD:C_0402_1005Metric,
C3,100n,Capacitor_SMD:C_0402_1005Metric,
C4,10u,Capacitor_SMD:C_0603_1608Metric,
C5,4.7u,Capacitor_SMD:C_0603_1608Metric,
C6,100n,Capacitor_SMD:C_0402_1005Metric,
C7,1u,Capacitor_SMD:C_0402_1005Metric,
C8,100n,Capacitor_SMD:C_0402_1005Metric,
C9,100n,Capacitor_SMD:C_0402_1005Metric,
C10,100n,Capacitor_SMD:C_0402_1005Metric,
R1,0R,Resistor_SMD:R_0402_1005Metric,
R2,10k,Resistor_SMD:R_0402_1005Metric,
R3,100k,Resistor_SMD:R_0402_1005Metric,
Y1,32.768kHz CL=7pF TBD,Crystal:Crystal_SMD_2012-2Pin_2.0x1.2mm,
C11,10p tentative,Capacitor_SMD:C_0402_1005Metric,
C12,10p tentative,Capacitor_SMD:C_0402_1005Metric,
J3,TC2030-CTX-NL-STDC14 target pads,Connector:Tag-Connect_TC2030-IDC-NL_2x03_P1.27mm_Vertical,TC2030 CTX mapping from vendor. SWO unused: PB3 reserved for ADF. VTref sense only. Reserve probe and rear retaining clip access; program before battery/case assembly.
SW1,B3U-1000P (candidate),Button_Switch_SMD:SW_SPST_B3U-1000P,
R4,100k,Resistor_SMD:R_0402_1005Metric,
R5,3.3k,Resistor_SMD:R_0402_1005Metric,
D1,red LED,LED_SMD:LED_0402_1005Metric,
J1,USB4105-GF-A (candidate),Connector_USB:USB_C_Receptacle_GCT_USB4105-xx-A_16P_TopMnt_Horizontal,Exact footprint and shield pad numbering pending connector selection
R6,5.1k 1%,Resistor_SMD:R_0402_1005Metric,
R7,5.1k 1%,Resistor_SMD:R_0402_1005Metric,
R8,22R tentative,Resistor_SMD:R_0402_1005Metric,
R9,22R tentative,Resistor_SMD:R_0402_1005Metric,
U2,USBLC6-2SC6,Package_TO_SOT_SMD:SOT-23-6,Verify footprint; short path to connector ground
C13,2.2u 10V,Capacitor_SMD:C_0402_1005Metric,
U3,BQ25101YFPR,Pendant:BQ25101_YFP6,"BQ25101, 21.81mA nominal with 6.19k 1%; TS NTC must contact cell. Temperature/timeout validation pending."
R10,6.19k 1%,Resistor_SMD:R_0402_1005Metric,BQ25101: nominal 21.81mA; KISET max145 / (6190*0.99)=23.66mA < DTP max55mA. Standard pack charging approximately22mA.
R11,100k,Resistor_SMD:R_0402_1005Metric,
C14,2.2u,Capacitor_SMD:C_0402_1005Metric,
J2,S2B-PH-SM4-TB(LF)(SN) / DTP401525 110mAh,Connector_JST:JST_PH_S2B-PH-SM4-TB_1x02-1MP_P2.00mm_Horizontal,"Two-pin PH pack connection. Confirm delivered polarity. TH1 is PCB-mounted thermal contact, no third battery wire."
TH1,NCP15XH103F03RC 10k NTC,Resistor_SMD:R_0402_1005Metric,PCB-mounted NTC thermally coupled to pack through insulation. Position/contact/thermal response require validation; no hand-soldered harness.
Q2,2N7002 (charge inhibit),Package_TO_SOT_SMD:SOT-23,High disables charging by pulling TS low; USB suspend policy required
R12,100k,Resistor_SMD:R_0402_1005Metric,
Q3,2N7002 (VBUS detect),Package_TO_SOT_SMD:SOT-23,
R13,100k,Resistor_SMD:R_0402_1005Metric,
R14,1M,Resistor_SMD:R_0402_1005Metric,
R15,100k,Resistor_SMD:R_0402_1005Metric,
D2,BAT54WS (candidate; leakage/forward drop review pending),Diode_SMD:D_SOD-323,USB path; characterize leakage and input inrush
Q1,DMP2035U (candidate; power path review pending),Package_TO_SOT_SMD:SOT-23,"S=SYS, D=BAT intentionally; body diode BAT -> SYS; exact MPN/pinout pending"
R16,100k,Resistor_SMD:R_0402_1005Metric,
C15,4.7u,Capacitor_SMD:C_0603_1608Metric,
U4,TPS7A0230PDBVR,Package_TO_SOT_SMD:SOT-23-5,DBV / SOT23-5 prototype; miniaturization later
U5,TPS7A0233PDBVR,Package_TO_SOT_SMD:SOT-23-5,DBV / SOT23-5 prototype; miniaturization later
U6,TPS7A0218PDBVR,Package_TO_SOT_SMD:SOT-23-5,DBV / SOT23-5 prototype; miniaturization later
C16,1u,Capacitor_SMD:C_0402_1005Metric,
C17,1u,Capacitor_SMD:C_0402_1005Metric,
C18,1u,Capacitor_SMD:C_0402_1005Metric,
C19,1u,Capacitor_SMD:C_0402_1005Metric,
C20,1u 10V,Capacitor_SMD:C_0402_1005Metric,
R17,100k,Resistor_SMD:R_0402_1005Metric,
U7,MAX17048G+T10,Package_DFN_QFN:TDFN-8-1EP_2x2mm_P0.5mm_EP0.8x1.2mm,EP pad number 9 is footprint convention; verify footprint
C21,100n,Capacitor_SMD:C_0402_1005Metric,
R18,4.7k,Resistor_SMD:R_0402_1005Metric,
R19,4.7k,Resistor_SMD:R_0402_1005Metric,
R20,100k,Resistor_SMD:R_0402_1005Metric,
U8,T5838,Pendant:T5838_LGA7_BottomPort,BOTTOM port; 1.62..1.98V only; SELECT low = right channel
U9,TXS0104EYZTR,Pendant:TXS0104E_YZT12,Omi MIC1 level translator and ball mapping; validate PDM waveform/loading
R21,22R tentative,Resistor_SMD:R_0402_1005Metric,
C22,100n,Capacitor_SMD:C_0402_1005Metric,
C23,100n,Capacitor_SMD:C_0402_1005Metric,
C24,100n,Capacitor_SMD:C_0402_1005Metric,
U10,TPS22916CYFPR,Pendant:TPS22916_YFP4,Omi SD switch; power-off sequence must tristate ALL SD signals
R22,100k,Resistor_SMD:R_0402_1005Metric,
C25,1u,Capacitor_SMD:C_0402_1005Metric,
U11,CSNP32GCR01-BOW,Pendant:CSNP32GCR01_LGA8,"4GB; LGA8 8x6.2mm; SD mode, NOT raw NAND"
R23,22R tentative,Resistor_SMD:R_0402_1005Metric,
R24,47k,Resistor_SMD:R_0402_1005Metric,
R25,47k,Resistor_SMD:R_0402_1005Metric,
R26,47k,Resistor_SMD:R_0402_1005Metric,
R27,47k,Resistor_SMD:R_0402_1005Metric,
R28,47k,Resistor_SMD:R_0402_1005Metric,
C26,100n,Capacitor_SMD:C_0402_1005Metric,
C27,22u effective TBD,Capacitor_SMD:C_0603_1608Metric,
TP1,TestPoint,TestPoint:TestPoint_Pad_D1.0mm,
TP2,TestPoint,TestPoint:TestPoint_Pad_D1.0mm,
TP3,TestPoint,TestPoint:TestPoint_Pad_D1.0mm,
TP4,TestPoint,TestPoint:TestPoint_Pad_D1.0mm,
TP5,TestPoint,TestPoint:TestPoint_Pad_D1.0mm,
TP6,TestPoint,TestPoint:TestPoint_Pad_D1.0mm,
TP7,TestPoint,TestPoint:TestPoint_Pad_D1.0mm,
R29,6.8k tentative,Resistor_SMD:R_0402_1005Metric,"LED current target 0.1-0.2mA; verify LED Vf, daylight readability and GPIO limits"
D3,amber LED 0402 TBD,LED_SMD:LED_0402_1005Metric,Battery segment 1
R30,6.8k tentative,Resistor_SMD:R_0402_1005Metric,"LED current target 0.1-0.2mA; verify LED Vf, daylight readability and GPIO limits"
D4,amber LED 0402 TBD,LED_SMD:LED_0402_1005Metric,Battery segment 2
R31,6.8k tentative,Resistor_SMD:R_0402_1005Metric,"LED current target 0.1-0.2mA; verify LED Vf, daylight readability and GPIO limits"
D5,amber LED 0402 TBD,LED_SMD:LED_0402_1005Metric,Battery segment 3
R32,6.8k tentative,Resistor_SMD:R_0402_1005Metric,"LED current target 0.1-0.2mA; verify LED Vf, daylight readability and GPIO limits"
D6,amber LED 0402 TBD,LED_SMD:LED_0402_1005Metric,Charge / sync / fault status; separate from recording LED

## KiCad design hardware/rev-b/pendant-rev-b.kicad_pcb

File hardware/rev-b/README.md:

# Rev B0 — アンテナ内蔵Bluetooth / 有線録音機

**製造リリース前。発注不可。** 回路図と実フットプリントを割り当てたPCBを作成し、配線を検証中。現状は **ERC 0、DRC 4（USB端子NPTHクリアランス）、未接続2（BAT/GND）**。`order-status.json` と `drc.json` を参照。Gerber/CPLの発注用ZIPは発行していない。

## 回路原本

- [design.json](design.json) / [KiCad回路図](pendant-rev-b.kicad_sch) / [回路図SVG](pendant-rev-b.svg)
- [KiCad PCB](pendant-rev-b.kicad_pcb) / [接続表](connections.csv) / [設計BOM](bom.csv)
- [部品調達照合](sourcing-review.json) / [ケースのSolidCraftモデル](../../mechanical/structure-b0/README.md)

Rev Aから独立した新回路。nRF52840を搭載するRaytac MDBT50Q-1MV2、T5838 PDMマイク、SPI接続4GB SD NAND、USB-C充電/MSC、BQ25101、MAX17048、保護付き110mAh既製電池を組み合わせる。68部品。ソフトv1は無線停止・有線同期、ソフトv2でBluetooth同期を目指す。

## 電気設計の変更

- STM32のSDMMCをSPIへ変更。SD NANDのDAT3=CS、CMD=DI、DAT0=DO、DAT1/2はSPI予約端子。資料の端子表と照合。
- モジュールVDDとVDDHを3.0Vへ接続、DCCHはNC。Raytac Ver.L p40の通常電圧構成。内蔵Reg1 DC/DCを使うファーム設定が必要。外部3.0V LDOを維持し、USB用3.3V LDOとSTM32固有回路を削除。
- VBUSはモジュールUSB用入力へ。USB挿入で録音状態を変える設計にはしない。27Ωシリーズ抵抗はメーカー参照値。
- RF付近の低周波専用GPIOにはボタン・表示・enable等を割当て、PDM/SPI/I2Cは通常GPIOに割当て。
- レベル変換はTXS0104EPWR/TSSOP-14へ変更。DSBGA中央パッドの引出しを避ける。TIのPW端子表と照合、JLC C44955掲載確認（確保/実装受理ではない）。
- 表示は録音1点＋共用状態1点。残量は短押し時の点滅回数等で表す案。実装/視認性試験は未完了。
- SWDは標準6接点を維持し、nRF対応プローブ/完成ケーブルを使う。STLINKをそのまま使えると扱わない。

## 基板・構造

22×43.5×0.8mm、4層。基板先端に全層RF禁止領域を設定。表面に主要回路、裏面にPH端子/NTC/測定接点を配置。USBシェル貫通穴と裏面PH端子が干渉しないよう左右に分離。電池はアンテナ領域を避け、コネクタと平面に並べる。構造案24.8×46.5×12.8mm。最小寸法を証明したものではない。

配線はFreeroutingで試行した結果をKiCadへ戻しDRCで検査する。ルータの「完了」は全結線や電気設計の正しさを保証しない。USB差動配線、連続GNDリターン、電源幅、デカップリング、RF、クリアランスのレビューが必要。

## 製造前の未解決事項

1. 全結線とDRC解消。USBフットプリントのNPTH付近のクリアランスは業者能力と図面の再照合が必要。違反を除外して合格にはしない。
2. USB入力10µF＋充電回路の入力容量による突入電流。容量のDCバイアス、USB規格、給電切替を検証し必要なら対策する。
3. モジュール、マイク、充電ICを含む全BOMの正確な品番・在庫・JLC Standard両面実装受理。全端子/フットプリント、極性、電池PH結線を監査。
4. 充電電流、保護電池条件、NTC熱結合、終止判定とUSB給電時の負荷分離をレビュー。
5. 完成品の書込み/測定治具、嵌合電池コネクタ・未加工リード線の実寸収納、ケース固定、マイク音道、装着方法。
6. 小型基板の製造パネル・治具・フィデューシャルをJLC条件へ合わせる。

24時間超の録音・36時間保存・ランダム電源断・暗号化・3 OS同期は、製作後のv1実機合格条件。回路図/ERCだけで合格や製品保証とはしない。

## 出典と再生成

[RaytacデータシートVer.L](https://www.raytac.com/download/index.php?index_id=43)、[TI TXS0104E](https://www.ti.com/lit/ds/symlink/txs0104e.pdf)、[SD NAND](https://datasheet.lcsc.com/lcsc/2410121341_CS-Semiconductor-CSNP32GCR01-BOW_C5440134.pdf)、[JLC製造能力](https://jlcpcb.com/capabilities/Capabilities)。2026-10-24照合。

`python3 hardware/tools/create_rev_b.py` → `generate_schematic.py rev-b`。PCBはKiCad同梱Pythonで `layout_rev_b.py`（配線を破棄して配置から再生成するため注意）→ `route_rev_b.py export` → Freerouting → `route_rev_b.py import`。実行した版とログはrouting/へ記録。配線後は `refine_rev_b.py` → `stitch_rev_b.py` → `cleanup_rev_b.py` でGNDポア・接続用ビアを追加/検査する。再実行時は配置から再生成する。0.15mmを通常配線幅とし、局所引出しの最小幅はJLC能力に合わせ0.10mm。クリアランス0.15mm、穴クリアランス0.20mm。DRC除外は設定していない。`verify_design.py <kicad-cli> rev-b` で接続表照合とERC。

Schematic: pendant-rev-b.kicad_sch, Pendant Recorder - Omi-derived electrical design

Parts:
C1, C9, C21, C22, C23, C24, C26: 100n; C_0402_1005Metric
C4: 10u; C_0603_1608Metric
C11, C12: 10p tentative; C_0402_1005Metric
C13: 2.2u 10V; C_0402_1005Metric
C14: 2.2u; C_0402_1005Metric
C15: 4.7u; C_0603_1608Metric
C16, C18, C19, C25: 1u; C_0402_1005Metric
C20: 10u 10V; C_0603_1608Metric
C27: 22u effective TBD; C_0603_1608Metric
D1: red LED; LED_0402_1005Metric
D2: BAT54WS (candidate; leakage/forward drop review p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; D_SOD-323
D6: amber LED 0402 TBD; LED_0402_1005Metric
J1: USB4105-GF-A (candidate); USB_C_Receptacle_GCT_USB4105-xx-A_16P_TopMnt_Horizontal
J2: S2B-PH-SM4-TB(LF)(SN) / DTP401525 110mAh; JST_PH_S2B-PH-SM4-TB_1x02-1MP_P2.00mm_Horizontal
J3: TC2030 SWD target pads; Tag-Connect_TC2030-IDC-NL_2x03_P1.27mm_Vertical
Q1: DMP2035U (candidate; power path review pending); SOT-23
Q2: 2N7002 (charge inhibit); SOT-23
R2: 10k; R_0402_1005Metric
R4, R11, R12, R16, R17, R20, R22: 100k; R_0402_1005Metric
R5: 3.3k; R_0402_1005Metric
R6, R7: 5.1k 1%; R_0402_1005Metric
R8, R9: 27R 1%; R_0402_1005Metric
R10: 6.19k 1%; R_0402_1005Metric
R18, R19: 4.7k; R_0402_1005Metric
R21, R23: 22R tentative; R_0402_1005Metric
R24, R25, R28: 47k; R_0402_1005Metric
R32: 6.8k tentative; R_0402_1005Metric
SW1: B3U-1000P (candidate); SW_SPST_B3U-1000P
TH1: NCP15XH103F03RC 10k NTC; R_0402_1005Metric
TP1, TP2, TP3, TP4, TP5, TP6: TestPoint; TestPoint_Pad_D1.0mm
U1: MDBT50Q-1MV2; Raytac_MDBT50Q
U2: USBLC6-2SC6; SOT-23-6
U3: BQ25101YFPR; BQ25101_YFP6
U4: TPS7A0230PDBVR; SOT-23-5
U6: TPS7A0218PDBVR; SOT-23-5
U7: MAX17048G+T10; TDFN-8-1EP_2x2mm_P0.5mm_EP0.8x1.2mm
U8: T5838; T5838_LGA7_BottomPort
U9: TXS0104EPWR; TSSOP-14_4.4x5mm_P0.65mm
U10: TPS22916CYFPR; TPS22916_YFP4
U11: CSNP32GCR01-BOW; CSNP32GCR01_LGA8
Y1: 32.768kHz CL=7pF TBD; Crystal_SMD_2012-2Pin_2.0x1.2mm

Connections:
BAT: C14.1, C21.1, J2.1 (PACK+), Q1.3 (D), TP1.1, U3.A1 (OUT), U7.2 (CELL), U7.3 (VDD)
BAT_ALERT_N: R20.2, U1.6 (P1.13), U7.5 (ALRT)
BAT_TS: Q2.3 (D), TH1.1, U3.B1 (TS)
BUTTON_N: R4.2, SW1.1, U1.5 (P1.12)
CC1: J1.A5 (CC1), R6.1
CC2: J1.B5 (CC2), R7.1
CHG_DISABLE: Q2.1 (G), R12.1, U1.8 (P1.15)
CHG_N: R11.2, U1.7 (P1.14), U3.C1 (CHG)
GND: C1.2, C4.2, C9.2, C11.2, C12.2, C13.2, C14.2, C15.2, C16.2, C18.2, C19.2, C20.2, C21.2, C22.2, C23.2, C24.2, C25.2, C26.2, C27.2, D1.1 (K), D6.1 (K), J1.A1 (GND), J1.A12 (GND), J1.B1 (GND), J1.B12 (GND), J1.SH (SHIELD), J2.2 (PACK-), J3.5 (GND), Q2.2 (S), R6.2, R7.2, R10.2, R12.2, R16.2, R17.2, R22.2, SW1.2, TH1.2, TP6.1, U1.1 (GND), U1.2 (GND), U1.15 (GND), U1.33 (GND), U1.55 (GND), U2.2 (GND), U3.C2 (VSS), U4.2 (GND), U6.2 (GND), U7.1 (CTG), U7.4 (GND), U7.6 (QSTRT), U7.9 (EP), U8.2 (SELECT), U8.3 (GND), U9.7 (GND), U10.B1 (GND), U11.4 (VSS)
I2C_SCL: R18.2, U1.16 (P0.27), U7.7 (SCL)
I2C_SDA: R19.2, U1.19 (P0.26), U7.8 (SDA)
ISET: R10.1, U3.B2 (ISET)
LED_A: D1.2 (A), R5.2
LSE_IN: C11.1, U1.17 (P0.00/XL1), Y1.1
LSE_OUT: C12.1, U1.18 (P0.01/XL2), Y1.2
MIC_CLK_1V8: U8.6 (CLK), U9.5 (A4)
MIC_DATA_1V8: U8.1 (DATA), U9.4 (A3)
MIC_EN: R17.1, U1.9 (P0.03), U6.3 (EN)
MIC_THSEL: U1.12 (P0.31), U9.12 (B2)
MIC_THSEL_1V8: U8.5 (THSEL), U9.3 (A2)
MIC_WAKE: U1.11 (P0.02), U9.13 (B1)
MIC_WAKE_1V8: U8.4 (WAKE), U9.2 (A1)
NRST: C9.1, J3.3 (nRESET), R2.2, U1.40 (P0.18/nRESET)
PDM_CLK: R21.2, U9.10 (B4)
PDM_CLK_MCU: R21.1, U1.36 (P0.14)
PDM_DATA: U1.37 (P0.13), U9.11 (B3)
REC_LED: R5.1, U1.3 (P1.10)
SD_CLK: R23.2, U11.3 (CLK)
SD_CLK_MCU: R23.1, U1.42 (P0.19)
SD_CS_N: R28.2, U1.45 (P0.23), U11.2 (CS_N)
SD_EN: R22.1, U1.10 (P0.29), U10.B2 (ON)
SD_MISO: R25.2, U1.43 (P0.21), U11.6 (DO)
SD_MOSI: R24.2, U1.44 (P0.20), U11.5 (DI)
SD_V3: C26.1, C27.1, R24.1, R25.1, R28.1, TP5.1, U10.A1 (VOUT), U11.8 (VCC)
STATUS_LED: R32.1, U1.4 (P1.11)
STATUS_LED_A: D6.2 (A), R32.2
SWCLK: J3.4 (SWCLK), U1.53 (SWDCLK)
SWDIO: J3.2 (SWDIO), U1.51 (SWDIO)
SYS: C15.1, D2.1 (K), Q1.2 (S), TP2.1, U4.1 (IN), U4.3 (EN)
USB_DM: J1.A7 (D-), J1.B7 (D-), R9.1, U2.3 (IO2), U2.4 (IO2)
USB_DM_MCU: R9.2, U1.34 (USB_D-)
USB_DP: J1.A6 (D+), J1.B6 (D+), R8.1, U2.1 (IO1), U2.6 (IO1)
USB_DP_MCU: R8.2, U1.35 (USB_D+)
V1V8: C18.1, C22.1, C23.1, TP4.1, U6.5 (OUT), U8.7 (VDD), U9.1 (VCCA), U9.8 (OE)
V3: C1.1, C4.1, C16.1, C19.1, C24.1, C25.1, J3.1 (VTref), R2.1, R4.1, R11.1, R18.1, R19.1, R20.1, TP3.1, U1.28 (VDD), U1.30 (VDDH), U4.5 (OUT), U6.1 (IN), U9.14 (VCCB), U10.A2 (VIN)
VBUS: C13.1, C20.1, D2.2 (A), J1.A4 (VBUS), J1.A9 (VBUS), J1.B4 (VBUS), J1.B9 (VBUS), Q1.1 (G), R16.1, U1.32 (VBUS), U2.5 (VBUS), U3.A2 (IN)

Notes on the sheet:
01 MCU / RTC / UI
02 USB-C / CHARGER
03 POWER / FUEL GAUGE
04 AUDIO / SD / INDICATORS
ENGINEERING DRAFT - NOT FOR FABRICATION - See hardware/rev-b/README.md
